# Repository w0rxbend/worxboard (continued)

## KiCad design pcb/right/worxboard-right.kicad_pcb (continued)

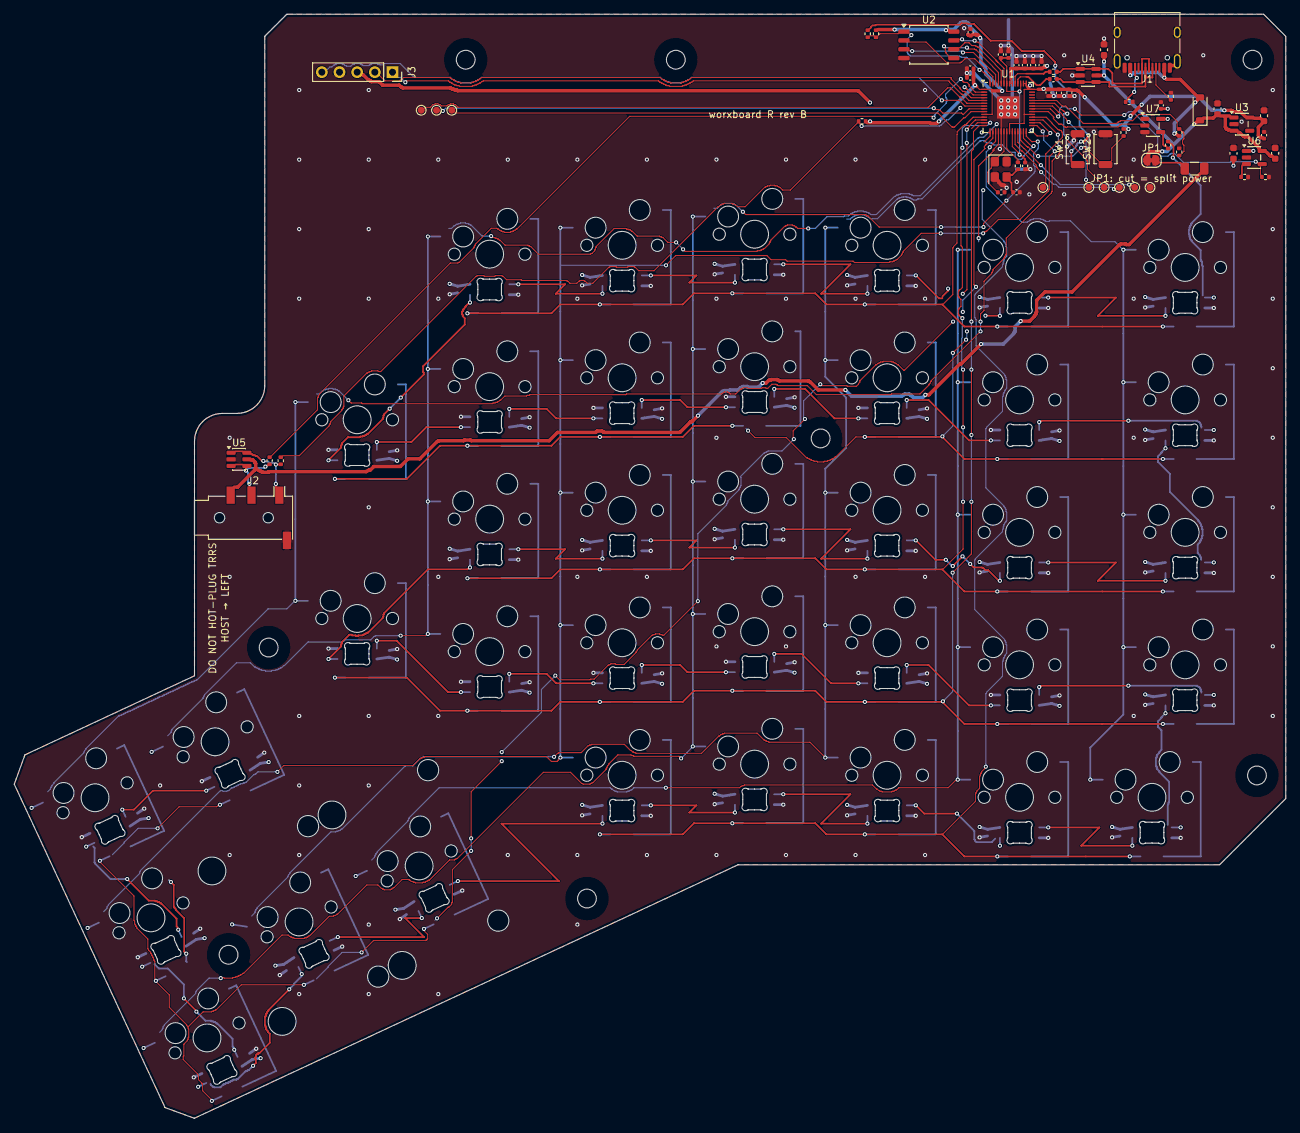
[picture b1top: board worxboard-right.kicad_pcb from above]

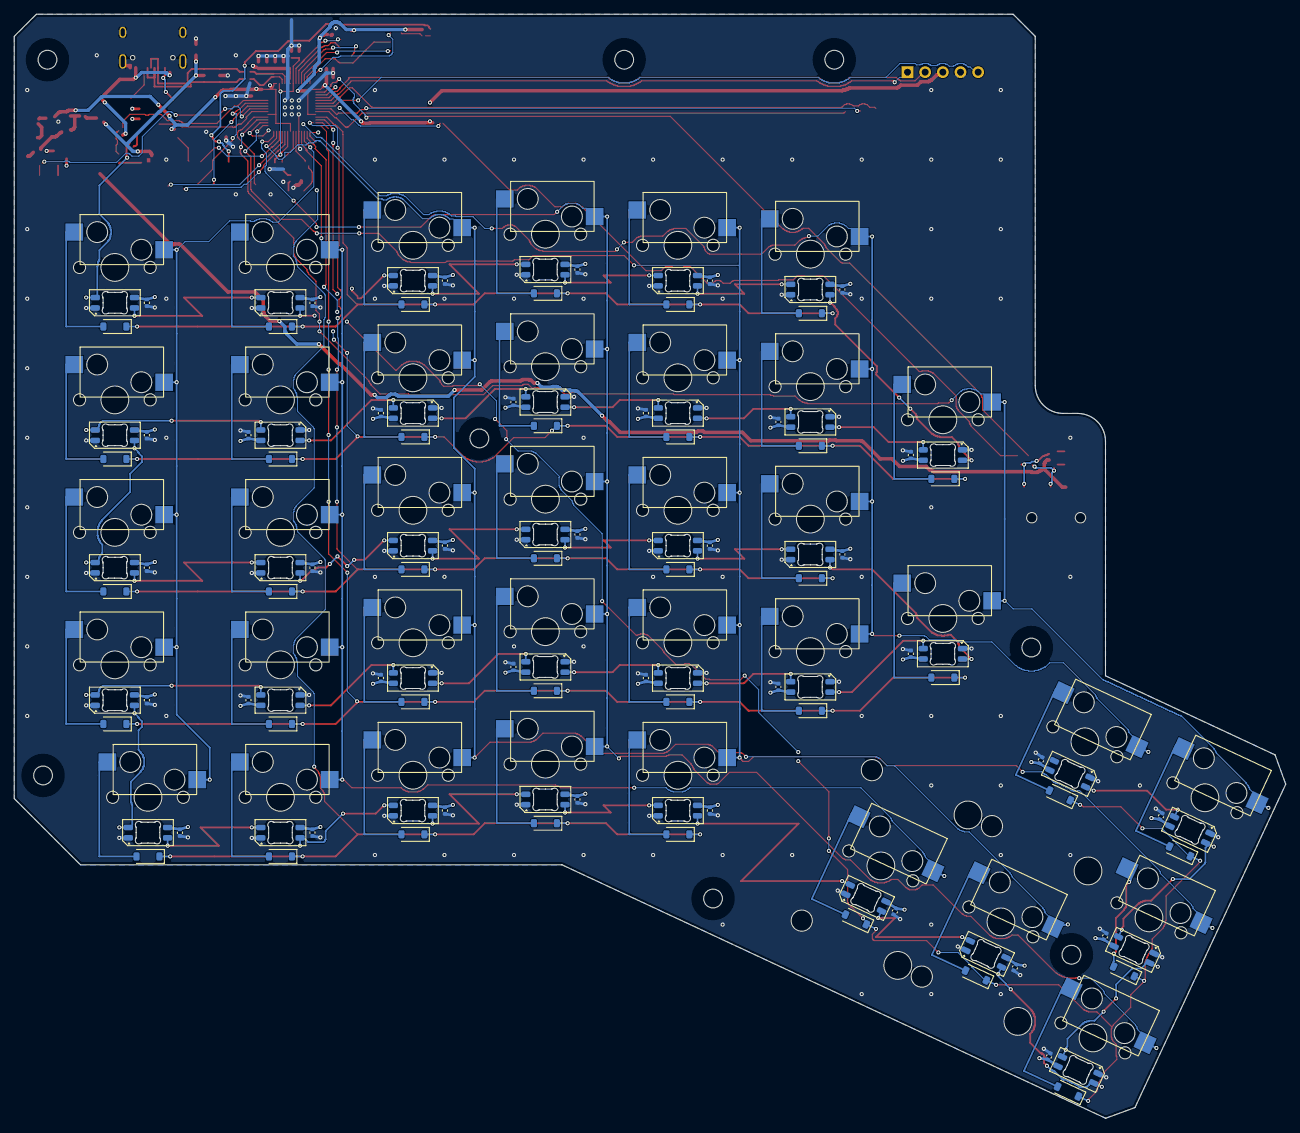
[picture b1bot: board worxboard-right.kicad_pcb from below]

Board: 4 copper layers, 182.8 x 158.8 mm, 221 parts (148 on the bottom side), 132 nets.

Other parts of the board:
STAB_T4, STAB_T5: Stab_MX_2u

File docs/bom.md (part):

# Bill of materials

Rev A (spec §7). JLCPCB buys and fits every part in the first table, on both sides, the display
socket J3 included: nothing is soldered on the PCB by hand. For an order, the files in
[`pcb/production/<side>/`](../pcb/production/) (`bom.csv`, `cpl.csv`) are the authority: see
[ordering-jlcpcb.md](ordering-jlcpcb.md). The tables below are generated from the same source
(`pcb/scripts/design.py`) and checked against both committed boards by `just docs-gen`. What you
buy yourself (switches, keycaps, displays, cables, screws) is in [shopping-list.md](shopping-list.md).

**Status key**

| Flag | Meaning |
|---|---|
| **[C]** | Verified from the Corne v4.1 JLC BOM ([foostan/crkbd](https://github.com/foostan/crkbd)) |
| **[J]** | Verified against JLC's own part record (library type, stock, assembly process) and its footprint (`pcb/scripts/cpl_check.py`) |
| G1, G2 | The part is what the display gate G1 or the TRRS jack gate G2 checks |

The spec's **[G3]** flags are gone: every one of those lines passed gate G3
([verification.md](verification.md#g3-parts-stock-and-track-width)).

## Per half, assembled by JLCPCB

Both halves have the same parts and references. The only difference between the two PCBs is the
TRRS TX/RX crossover in the netlist (R11/R12). Matrix parts are numbered per key: socket `SK<n>`
and diode `D<n>`, n = 101…137 in [matrix.md](matrix.md#sockets-and-diodes) order.

<!-- BEGIN GENERATED: bom_assembled (site/gen_docs.py from pcb/scripts/design.py; run `just docs-gen`) -->
| Designators | Qty | Part | LCSC | Footprint | Side | Status | Extended |
|---|---|---|---|---|---|---|---|
| U1 | 1 | RP2040 microcontroller | [C2040](https://jlcpcb.com/partdetail/C2040) | `QFN-56-1EP_7x7mm_P0.4mm_EP3.2x3.2mm` | top | [C] | yes |
| U2 | 1 | W25Q128JVSIQ, 16 MB QSPI flash | [C97521](https://jlcpcb.com/partdetail/C97521) | `SOIC-8_5.3x5.3mm_P1.27mm` | top | [J] |  |
| C5, C8–C17, C22, C101–C137 | 49 | 100 nF 0402 | [C1525](https://jlcpcb.com/partdetail/C1525) | `C_0402_1005Metric` | top 12, **bottom** 37 | [C] |  |
| Y1 | 1 | 12 MHz crystal, CL 10 pF, ESR 50 Ω, 3225 (Abracon ABM8-272-T3; REVB-10: was YXC C49304726) | [C20625731](https://jlcpcb.com/partdetail/C20625731) | `Crystal_SMD_3225-4Pin_3.2x2.5mm` | top | [J] | yes |
| R7, R9 | 2 | 1 kΩ 0402 | [C11702](https://jlcpcb.com/partdetail/C11702) | `R_0402_1005Metric` | top | [C] |  |
| C6, C7 | 2 | 15 pF 0402 C0G (crystal load; REVB-10: was 27 pF) | [C1548](https://jlcpcb.com/partdetail/C1548) | `C_0402_1005Metric` | top | [J] |  |
| R5, R6, R8, R10, R13, R15 | 6 | 10 kΩ 0402 | [C25744](https://jlcpcb.com/partdetail/C25744) | `R_0402_1005Metric` | top | [C] |  |
| SW1 | 1 | TS-1088R-02026 tact switch (BOOT) | [C455280](https://jlcpcb.com/partdetail/C455280) | `SW_SPST_TS-1088-xR020` | top | [C] | yes |
| SW2 | 1 | TS-1088R-02026 tact switch (RESET) | [C455280](https://jlcpcb.com/partdetail/C455280) | `SW_SPST_TS-1088-xR020` | top | [C] | yes |
| C4, C18, C19 | 3 | 1 µF 0402 | [C52923](https://jlcpcb.com/partdetail/C52923) | `C_0402_1005Metric` | top | [C] |  |
| J1 | 1 | HRO TYPE-C-31-M-12, USB-C 16P | [C165948](https://jlcpcb.com/partdetail/C165948) | `USB_C_Receptacle_HRO_TYPE-C-31-M-12` | top | [J] | yes |
| R1, R2 | 2 | 5.1 kΩ 0402 | [C25905](https://jlcpcb.com/partdetail/C25905) | `R_0402_1005Metric` | top | [C] |  |
| R3, R4 | 2 | 27 Ω 0402 | [C2909343](https://jlcpcb.com/partdetail/C2909343) | `R_0402_1005Metric` | top | [C] | yes |
| U4, U5 | 2 | USBLC6-2SC6 ESD array (USB, TRRS) | [C7519](https://jlcpcb.com/partdetail/C7519) | `SOT-23-6` | top | [J] | yes |
| D1 | 1 | B5819W, 1 A Schottky | [C8598](https://jlcpcb.com/partdetail/C8598) | `D_SOD-123` | top | [J] |  |
| C1–C3, C20, C21 | 5 | 10 µF 0603, 10 V X5R (rev B: was 0402 6.3 V) | [C19702](https://jlcpcb.com/partdetail/C19702) | `C_0603_1608Metric` | top | [J] |  |
| U3 | 1 | AP2112K-3.3TRG1, 600 mA LDO | [C51118](https://jlcpcb.com/partdetail/C51118) | `SOT-23-5` | top | [J] | yes |
| F1 | 1 | nSMD050-24V PTC, 500 mA hold, 24 V (REVB-9: was nSMD025-24V) | [C70076](https://jlcpcb.com/partdetail/C70076) | `Fuse_1206_3216Metric` | top | [J] | yes |
| J2 | 1 | PJ-320D-4A TRRS jack, SMD | [C95562](https://jlcpcb.com/partdetail/C95562) | `Jack_3.5mm_PJ320D_Horizontal` | top | [J], G2 | yes |
| R11, R12, R16 | 3 | 470 Ω 0402 (LED data and UART series) | [C25117](https://jlcpcb.com/partdetail/C25117) | `R_0402_1005Metric` | top | [J] |  |
| J3 | 1 | 1×5 2.54 mm female socket, 5.0 mm, **THT** (display, G1) | [C27985230](https://jlcpcb.com/partdetail/C27985230) | `PinSocket_1x05_P2.54mm_Vertical_H5.0mm` | top | [J], G1 | yes |
| U6 | 1 | SY6280AAC VLED load switch, 0.45 A limit (rev B) | [C55136](https://jlcpcb.com/partdetail/C55136) | `SOT-23-5` | top | [J] | yes |
| R14 | 1 | 15 kΩ 0402 (U6 current limit) | [C25756](https://jlcpcb.com/partdetail/C25756) | `R_0402_1005Metric` | top | [J] |  |
| U7 | 1 | SN74LV1T34DBVR 3.3 V -> VLED data buffer (rev B) | [C100024](https://jlcpcb.com/partdetail/C100024) | `SOT-23-5` | top | [J] | yes |
| LED101–LED137 | 37 | SK6812MINI-E RGB LED, reverse mount through a PCB cutout (rev B) | [C5149201](https://jlcpcb.com/partdetail/C5149201) | `LED_SK6812MINI-E_ReverseMount` | **bottom** | [J] | yes |
| SK101–SK137 | 37 | MX hot-swap socket CPG151101S11-16 (HanElectricity) | [C41430893](https://jlcpcb.com/partdetail/C41430893) | `SW_MX_Hotswap_Kailh` | **bottom** | [J] | yes |
| D101–D137 | 37 | 1N4148W switching diode | [C81598](https://jlcpcb.com/partdetail/C81598) | `D_SOD-123` | **bottom** | [J] |  |

27 BOM lines, 201 parts per half, 148 of them on the bottom side.
<!-- END GENERATED: bom_assembled -->

- **Stock.** Check it on the day you order: `just pcb-stock left 5` (both halves draw on the same
  stock). On 2026-11-04 at 05:17 UTC every rev A line passed for 5 assembled boards per half. The
  thinnest were C95562 (5 513), C27985230 (6 294), C51118 (12 075) and C49304726 (13 833). The lines
  rev B adds or changes (C5149201, C55136, C100024, C19702, C70076, C25117) have not been
  stock-checked yet. Alternates are in
  [ordering-jlcpcb.md](ordering-jlcpcb.md#if-a-part-is-out-of-stock).
- **Replaced parts.** The discontinued Kailh socket C2803348, the flash C113767 and the low-stock
  crystal C91749 were replaced by C41430893, C97521 and C49304726 (deviation ELEC-1). `stock.py` and
  `netcmp.py` fail if one of the retired numbers comes back.
- **J3** is the only through-hole part, a 5.0 mm socket that JLC hand-solders (ELEC-3). A stock
  nice!view plugs into it on its own header.
- **F1** is the nSMD050-24V, 500 mA hold (C70076, deviation REVB-9). Rev A used WS2's choice for the
  spec's "PTC 1206, 250 mA hold", C70069 (deviation WS2a-4).
- **Placement.** `cpl.csv` carries a JLC correction for U1, U2, U3–U5, U7, J1, J2, J3 and the
  sockets (`pcb/scripts/jlc_rotations.csv`, U7 per part, REVB-1). `cpl_check.py` proved every placement
  against JLC's own footprint of the part: 201 of 201 per half (PKG-2). The table is in
  [ordering-jlcpcb.md](ordering-jlcpcb.md#how-the-package-is-made-and-checked). JLC's preview draws its
  own footprint of each part. Check it as
  [ordering-jlcpcb.md](ordering-jlcpcb.md#placement-preview-checklist) describes, because JLC does not
  document its bottom-side convention.

## Not in the JLC BOM or placement file

These footprints are copper or holes only. They are marked "exclude from BOM / position files" on
the boards, and stage D fails if one of them reaches `bom.csv` or `cpl.csv` (`netcmp.py --board`,
deviation ELEC-6).

<!-- BEGIN GENERATED: bom_excluded (site/gen_docs.py from the committed boards; run `just docs-gen`) -->
| Designators | Qty | What | Why |
|---|---|---|---|
| JP1 | 1 | solder jumper VSYS → F1 → VLINK, bridged | copper only; cut it for split-powered mode |
| TP1–TP3, TP6–TP11 | 9 | Ø1.0 mm test pads: TP1 `DISP_DC`, TP2 `DISP_RST`, TP3 `DISP_BL`, TP6 GP24, TP7 GP25, TP8 `SWCLK`, TP9 `SWDIO`, TP10 `GND`, TP11 `TRRS_DET` | copper only |
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
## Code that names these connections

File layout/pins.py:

# SPDX-License-Identifier: GPL-3.0-or-later
"""RP2040 GPIO map (spec §3). FROZEN contract, identical on both PCBs.

Pin names are the KiCad 10 `MCU_RaspberryPi:RP2040` symbol names (the authority);
QFN numbers are informational.
"""
from __future__ import annotations

from dataclasses import dataclass


@dataclass(frozen=True)
class Pin:
    name: str            # RP2040 symbol pin name
    qfn: int
    net: str | None      # None = no connection
    note: str = ""


ROW_GPIOS = tuple(range(8, 14))          # ROW0..ROW5, inputs with pull-down
COL_GPIOS = tuple(range(14, 21))         # COL0 (outer)..COL6 (inner), outputs
RIGHT_COL_GPIOS = COL_GPIOS[::-1]        # right .dts lists GP20..GP14 (col-offset 7)
UART_TX, UART_RX = 0, 1
UART_BAUD = 115200
DISP_SCK, DISP_MOSI, DISP_CS = 2, 3, 5   # PIO1 SPI; CS is active high
# Per-key RGB (rev B): GP22 -> U7 SN74LV1T34 (3.3 V -> VLED) -> 470R -> LED101 DIN, WS2812 protocol on
# PIO0; GP23 -> U6 SY6280AAC EN (VSYS -> VLED, active high, 10k pull-down: LEDs off until the
# firmware enables them, ZMK ext-power)
RGB_DATA, RGB_EN = 22, 23

_COL_QFN = (17, 18, 27, 28, 29, 30, 31)

PINS: list[Pin] = [
    Pin("GPIO0", 2, "UART_TX", "UART0 TX -> 470R -> jack"),
    Pin("GPIO1", 3, "UART_RX", "UART0 RX <- 470R <- jack; 10k pull-up to 3V3"),
    Pin("GPIO2", 4, "DISP_SCK", "PIO1 SPI clock"),
    Pin("GPIO3", 5, "DISP_MOSI", "PIO1 SPI data"),
    Pin("GPIO4", 6, "DISP_DC", "TP1 (future TFT)"),
    Pin("GPIO5", 7, "DISP_CS", "display CS, active high"),
    Pin("GPIO6", 8, "DISP_RST", "TP2 (future TFT)"),
    Pin("GPIO7", 9, "DISP_BL", "TP3 (future TFT backlight)"),
    *(Pin(f"GPIO{g}", 11 + i, f"ROW{i}", "matrix row, pull-down") for i, g in enumerate(ROW_GPIOS)),
    *(Pin(f"GPIO{g}", q, f"COL{i}", "matrix column") for i, (g, q) in enumerate(zip(COL_GPIOS, _COL_QFN))),
    Pin("GPIO21", 32, "TRRS_DET", "test pad (future detect-gpios)"),
    Pin("GPIO22", 34, "RGB_DIN", "per-key RGB data (PIO0 WS2812) -> U7 level shifter"),
    Pin("GPIO23", 35, "RGB_EN", "U6 VLED switch enable, active high, 10k pull-down"),
    Pin("GPIO24", 36, "TP6", "spare"),
    Pin("GPIO25", 37, "TP7", "spare"),
    Pin("GPIO26/ADC0", 38, "VBUS_SENSE", "VBUS 10k/10k divider, unused by rev A"),
    Pin("GPIO27/ADC1", 39, None),
    Pin("GPIO28/ADC2", 40, None),
    Pin("GPIO29/ADC3", 41, None),
    Pin("~{QSPI_SS}", 56, "QSPI_SS", "flash CS, 10k pull-up; BOOT -> 1k -> GND"),
    Pin("RUN", 26, "RUN", "10k pull-up; RESET -> GND"),
    Pin("SWCLK", 24, "SWCLK", "SWD test pad"),
    Pin("SWDIO", 25, "SWDIO", "SWD test pad"),
    Pin("TESTEN", 19, "GND"),
    Pin("XIN", 20, "XIN", "12 MHz crystal"),
    Pin("XOUT", 21, "XOUT", "1k series to crystal"),
    Pin("USB_DM", 46, "USB_DM", "27R series"),
    Pin("USB_DP", 47, "USB_DP", "27R series"),
]

BY_NET = {p.net: p for p in PINS if p.net}

# TRRS contacts per side (spec §6.2): the TX/RX crossover is in the netlist
TRRS = {
    "left": {"T": "TRRS_A", "R1": "TRRS_B", "R2": "VLINK", "S": "GND",
             "TRRS_A": "UART_TX", "TRRS_B": "UART_RX"},
    "right": {"T": "TRRS_A", "R1": "TRRS_B", "R2": "VLINK", "S": "GND",
              "TRRS_A": "UART_RX", "TRRS_B": "UART_TX"},
}


def gpio(net: str) -> int:
    """GPIO number of a GPIO net, e.g. gpio('COL3') == 17."""
    name = BY_NET[net].name
    return int(name[4:].split("/")[0])
